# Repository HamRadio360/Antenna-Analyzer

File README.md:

# K6BEZ Antenna Analyzer

The K6BEZ antenna analyzer will provide VSWR measurements for any antenna from 1 to 30 MHz.  Frequency and VSWR is shown on the built in LCD display.  Data can optionally be sent over the USB cable to a PC running a program that will plot the VSWR on a graphical window display.
The analyzer can be programmed to scan any sub band and has built in ranges for 160m, 80m, 60m, 40m, 30m, 20m, 17m, 15m, 12m, 10m. 

For more information check out the [project website](http://www.360workbench.com/) and the [Ham Radio 360 forum](http://hamradio360.com/community/main-forum/).

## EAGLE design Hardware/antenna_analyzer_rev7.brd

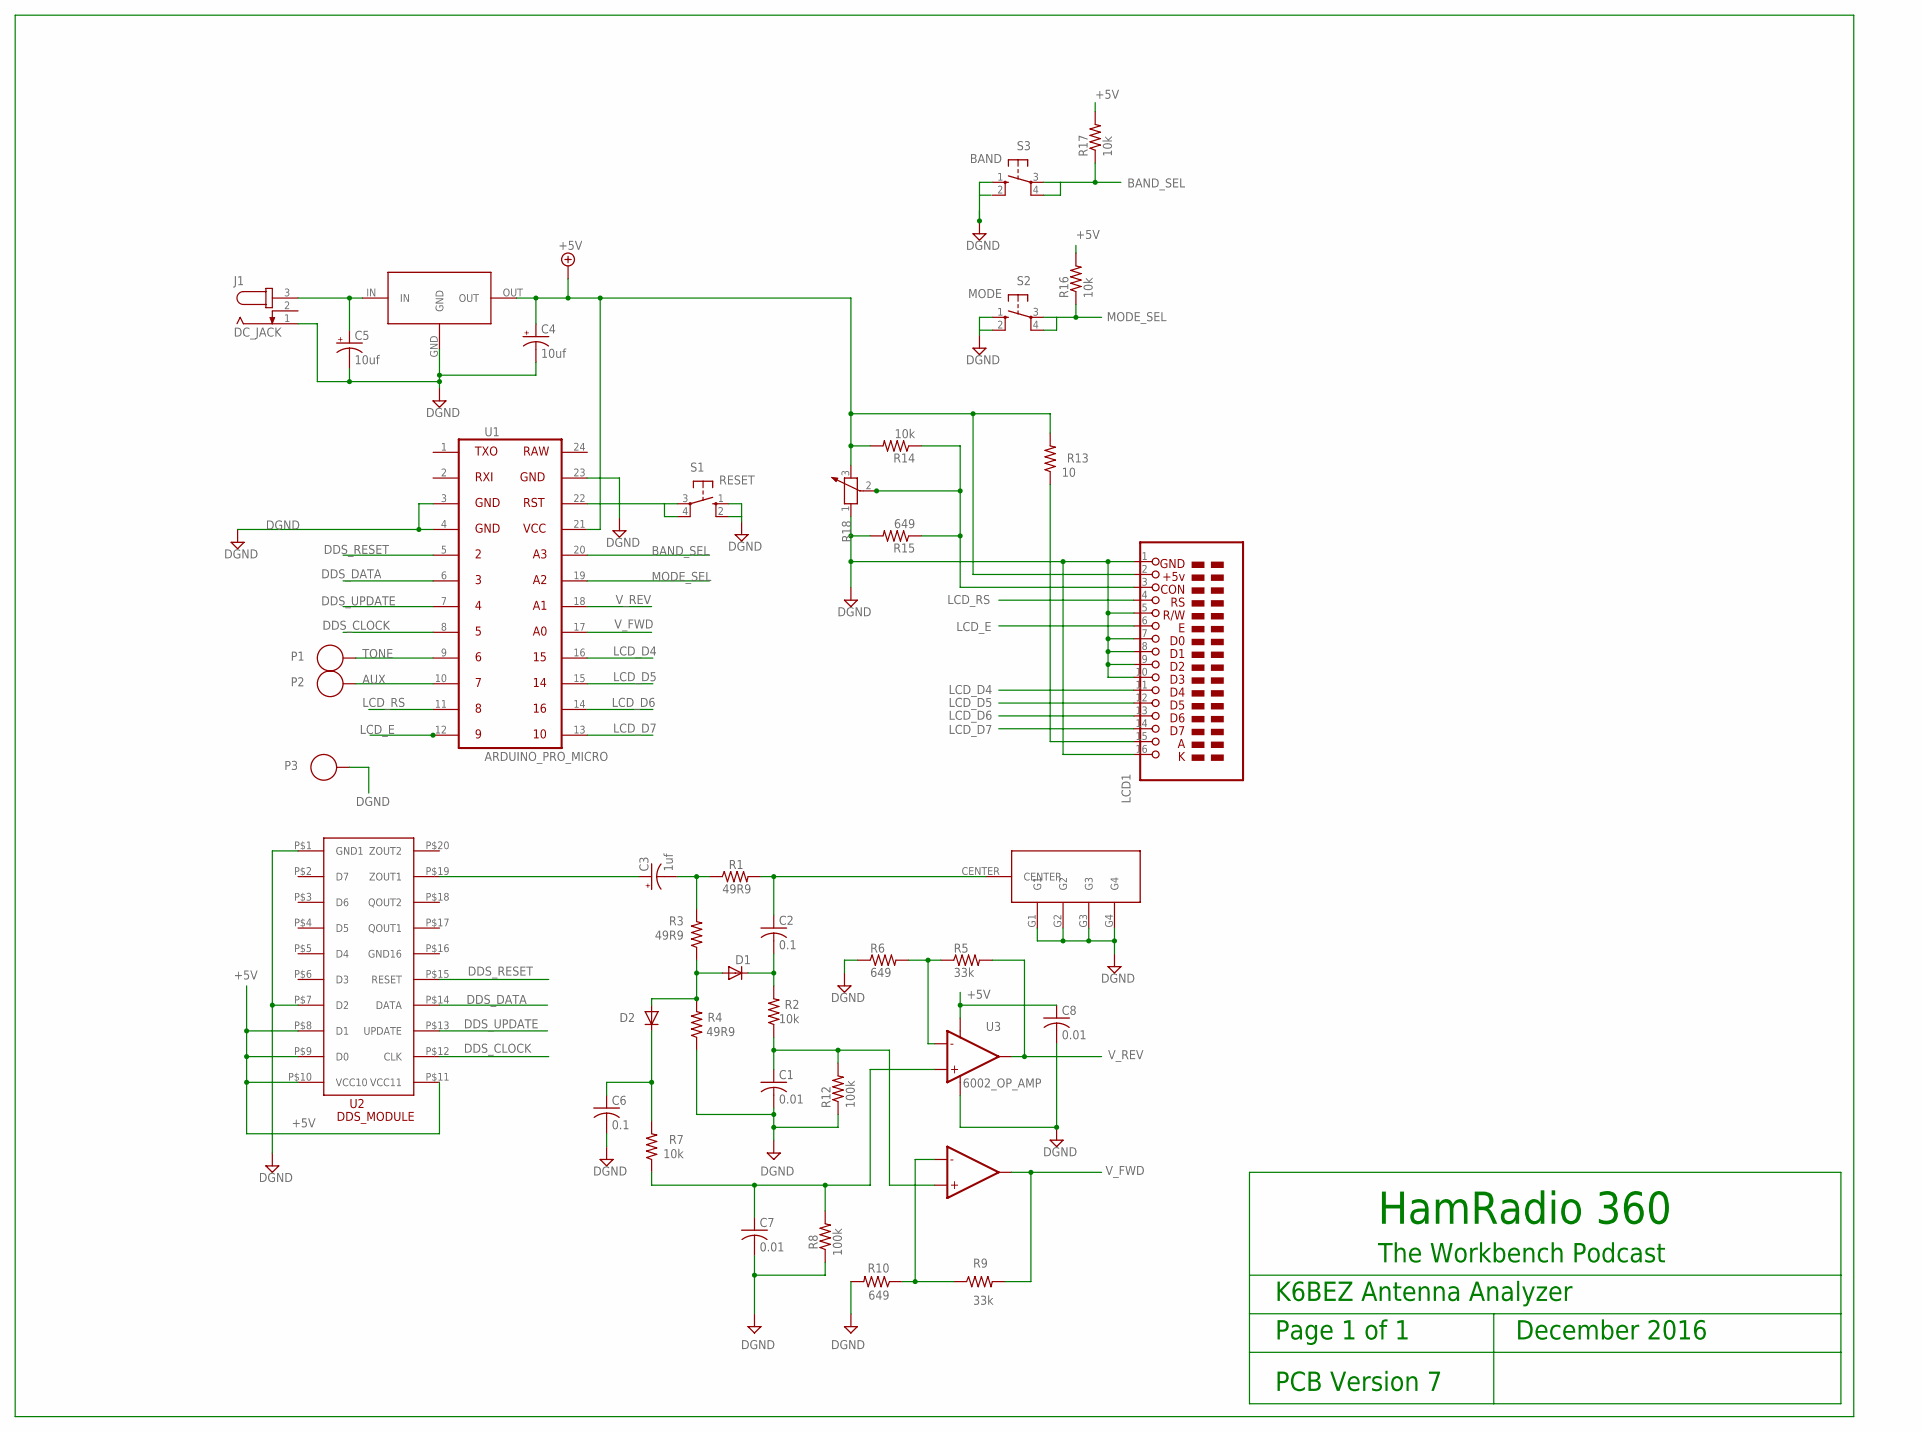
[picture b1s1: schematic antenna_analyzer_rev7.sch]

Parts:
C1, C7, C8: 0.01; C025-025X050
C2, C6: 0.1; C025-025X050
C3: 1uf; E1,8-4
C4, C5: 10uf; E1,8-4
CON1: BNC-SMALL
D1, D2: AA143; DO35-7
J1: DC_JACK; DC_COAXIAL_JACK
LCD1: LCD_2_16; LCD_2X16
P1, P2, P3: SOLDER_PAD_35_HOLE
R1, R3, R4: 49R9; 0207/10
R2, R7, R14, R16, R17: 10k; 0207/10
R5, R9: 33k; 0207/10
R6, R10, R15: 649; 0207/10
R8, R12: 100k; 0207/10
R13: 10; 0207/10
R18: R-POTENTIOMETER-3362U; 3362U
S1: RESET; B3F-10XX
S2: MODE; B3F-10XX
S3: BAND; B3F-10XX
U1: ARDUINO_PRO_MICRO
U2: AD9850_MOD; DDS_DIL
U3: 6002_OP_AMP; OP_AMP_8_PIN
U5: SWITCHING_REGULATOR

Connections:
+5V: C4.+, C8.1, LCD1.2, R13.2, R14.2, R16.2, R17.2, R18.3 (2), U1.21, U2.P$8 (D1), U2.P$9 (D0), U2.P$10 (VCC10), U2.P$11 (VCC11), U3.8 (VCC+), U5.OUT
AUX: P2.1, U1.10
BAND_SEL: R17.1, S3.3, S3.4 (P1), U1.20
DDS_CLOCK: U1.8, U2.P$12 (CLK)
DDS_DATA: U1.6, U2.P$14 (DATA)
DDS_RESET: U1.5, U2.P$15 (RESET)
DDS_UPDATE: U1.7, U2.P$13 (UPDATE)
DGND: C1.2, C4.-, C5.-, C6.2, C7.2, C8.2, CON1.G1, CON1.G2, CON1.G3, CON1.G4, J1.1, LCD1.1, LCD1.5, LCD1.7, LCD1.8, LCD1.9, LCD1.10, LCD1.16, P3.1, R4.1, R6.1, R8.1, R10.2, R12.1, R15.2, R18.1, S1.1 (S), S1.2 (S1), S2.1 (S), S2.2 (S1), S3.1 (S), U1.3, U1.4, U1.23, U2.P$1 (GND1), U2.P$7 (D2), U3.4 (VCC-), U5.GND
LCD_D4: LCD1.11, U1.16
LCD_D5: LCD1.12, U1.15
LCD_D6: LCD1.13, U1.14
LCD_D7: LCD1.14, U1.13
LCD_E: LCD1.6, U1.12
LCD_RS: LCD1.4, U1.11
MODE_SEL: R16.1, S2.3, S2.4 (P1), U1.19
unnamed: C5.+, J1.3, U5.IN
unnamed: C6.1, D2.C, R7.2
unnamed: C3.+, U2.P$19 (ZOUT1)
unnamed: C3.-, R1.1, R3.2
unnamed: D1.A, D2.A, R3.1, R4.2
unnamed: C2.1, CON1.CENTER, R1.2
unnamed: C2.2, D1.C, R2.2
unnamed: C1.1, R2.1, R12.2, U3.5 (IN+2)
unnamed: C7.1, R7.1, R8.2, U3.3 (IN+1)
unnamed: S1.3, S1.4 (P1), U1.22
unnamed: R9.1, R10.1, U3.6 (IN-2)
unnamed: R5.1, R6.2, U3.2 (IN-1)
unnamed: LCD1.15, R13.1
unnamed: LCD1.3, R14.1, R15.1, R18.2 (3)
TONE: P1.1, U1.9
V_FWD: R9.2, U1.17, U3.7 (OUT2)
V_REV: R5.2, U1.18, U3.1 (OUT1)

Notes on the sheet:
HamRadio 360
The Workbench Podcast
K6BEZ Antenna Analyzer
Page 1 of 1 December 2016
PCB Version 7

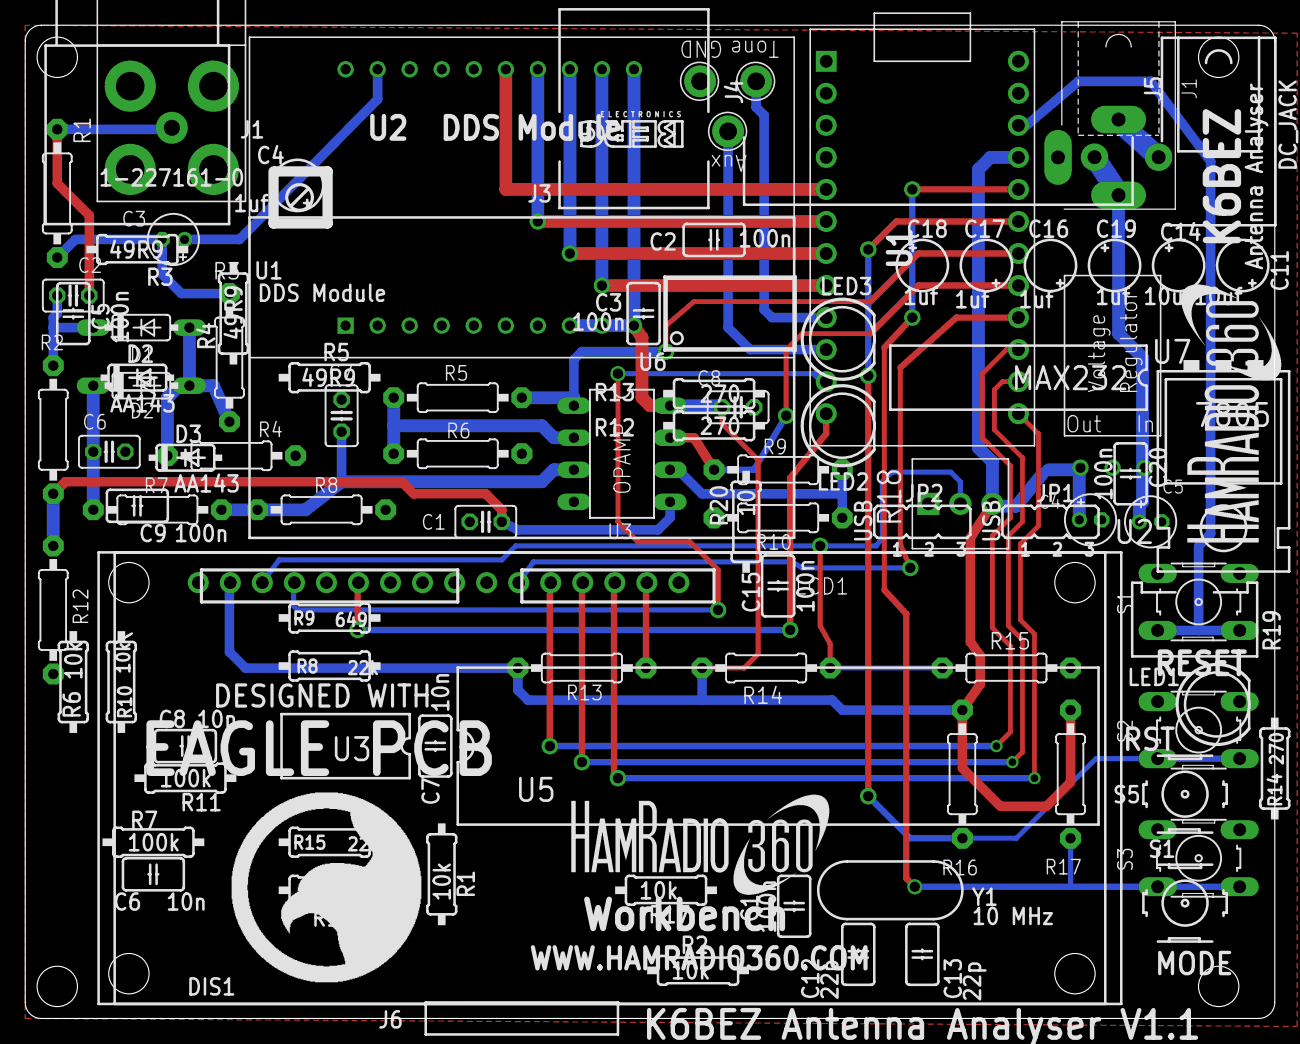
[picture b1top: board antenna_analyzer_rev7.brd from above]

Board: 2 copper layers, 99.1 x 78.7 mm, 42 parts (1 on the bottom side), 32 nets.

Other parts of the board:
U$1, U$2: CS-2016-LOGO-15MM

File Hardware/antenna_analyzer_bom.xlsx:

HamRadio 360 Workbench - K6BEZ Antenna Analyzer Bill of Materials
Type | Part | Description | Value | Digikey Part # | Est Price | Web Site
Connector | CON1 | Right angle BNC connector |  | A97569-ND | 3.88
Connector | J1 | DC power jack 2.1mm |  | CP-102AH-ND | 1.18
Capacitor | C1 | 0.1" spaced dipped mono 10% | 0.01 | 399-4260-ND | 0.24
Capacitor | C2 | 0.1" spaced dipped mono 10% | 0.1 | BC1084CT-ND | 0.22
Capacitor | C3 | Electrolytic capacitor 25v | 1uf | 493-10461-1-ND | 0.1
Capacitor | C4 | Electrolytic capacitor 25v | 10uf | P980-ND | 0.23
Capacitor | C5 | Electrolytic capacitor 25v | 10uf | P980-ND | 0.23
Capacitor | C6 | 0.1" spaced dipped mono 10% | 0.1 | BC1084CT-ND | 0.22
Capacitor | C7 | 0.1" spaced dipped mono 10% | 0.01 | 399-4260-ND | 0.24
Capacitor | C8 | 0.1" spaced dipped mono 10% | 0.01 | 399-4260-ND | 0.24
Resistor | R1 | 1/4 Watt 5% | 49.9 | 49.9XBK-ND | 0.1
Resistor | R2 | 1/4 Watt 5% | 10k | 10KQBK-ND | 0.1
Resistor | R3 | 1/4 Watt 5% | 49.9 | 49.9XBK-ND | 0.1
Resistor | R4 | 1/4 Watt 5% | 49.9 | 49.9XBK-ND | 0.1
Resistor | R5 | 1/4 Watt 5% | 649 | 649XBK-ND | 0.1
Resistor | R6 | 1/4 Watt 5% | 33k | 33KQBK-ND | 0.1
Resistor | R7 | 1/4 Watt 5% | 10k | 10KQBK-ND | 0.1
Resistor | R8 | 1/4 Watt 5% | 100k | 100KQBK-ND | 0.1
Resistor | R9 | 1/4 Watt 5% | 649 | 649XBK-ND | 0.1
Resistor | R10 | 1/4 Watt 5% | 33k | 33KQBK-ND | 0.1
Resistor | R12 | 1/4 Watt 5% | 100k | 100KQBK-ND | 0.1
Resistor | R13 | 1/4 Watt 5% | 10 | 10QBK-ND | 0.1
Resistor | R14 | 1/4 Watt 5% | 10k | 10KQBK-ND | 0.1
Resistor | R15 | 1/4 Watt 5% | 649 | 649XBK-ND | 0.1
Resistor | R16 | 1/4 Watt 5% | 10k | 10KQBK-ND | 0.1
Resistor | R17 | 1/4 Watt 5% | 10k | 10KQBK-ND | 0.1
Switch | S1 | Tactile pushbutton switch |  | 450-1650-ND | 0.1
Switch | S2 | Tactile pushbutton switch |  | 450-1650-ND | 0.1
Switch | S3 | Tactile pushbutton switch |  | 450-1650-ND | 0.1
Integrated Circuit | U3 | MCP 6002 Dual OpAmp |  | MCP6002-E/P-ND | 0.36
Integrated Circuit | U4 | 5v DC / DC converter OKI-78SR-5/1.5-W36H-C |  | 811-2692-ND | 4.31
Mechanical | X1 | 10 pin female header |  | S7043-ND | 0.85
Mechanical | X2 | 10 pin female header |  | S7043-ND | 0.85
Mechanical | X3 | 16 pin male header 0.1" pitch |  | S1011EC-16-ND | 0.4
Mechanical | X4 | 4-40 Hex standoff 1/4" long, 3/16" diameter |  | 36-1891-ND | 0.4
Mechanical | X5 | 4-40 Hex standoff 1/4" long, 3/16" diameter |  | 36-1891-ND | 0.4
Mechanical | X6 | 4-40 Hex standoff 1/4" long, 3/16" diameter |  | 36-1891-ND | 0.4
Mechanical | X7 | 4-40 Hex standoff 1/4" long, 3/16" diameter |  | 36-1891-ND | 0.4
Mechanical | X8 | 4-40 Hex standoff 1/4" long, 3/16" diameter |  | 36-1891-ND | 0.4
Mechanical | X9 | 4-40 Hex standoff 1/4" long, 3/16" diameter |  | 36-1891-ND | 0.4
Mechanical | X10 | 4-40 Hex standoff 1/4" long, 3/16" diameter |  | 36-1891-ND | 0.4
Mechanical | X11 | 4-40 Hex standoff 1/4" long, 3/16" diameter |  | 36-1891-ND | 0.4
Mechanical | X12 | 4-40 1/4" pan head philips screw |  | 36-9900-ND | 0.1
Mechanical | X13 | 4-40 1/4" pan head philips screw |  | 36-9900-ND | 0.1
Mechanical | X14 | 4-40 1/4" pan head philips screw |  | 36-9900-ND | 0.1
Mechanical | X15 | 4-40 1/4" pan head philips screw |  | 36-9900-ND | 0.1
Mechanical | X16 | 4-40 hex nut |  | 36-4694-ND | 0.08
Mechanical | X17 | 4-40 hex nut |  | 36-4694-ND | 0.08
Mechanical | X18 | 4-40 hex nut |  | 36-4694-ND | 0.08
Mechanical | X19 | 4-40 hex nut |  | 36-4694-ND | 0.08
Mechanical | X20 | 4-40 1/2" pan head philips screw |  | 36-9902-ND | 0.12
Mechanical | X21 | 4-40 1/2" pan head philips screw |  | 36-9902-ND | 0.12
Mechanical | X22 | 4-40 1/2" pan head philips screw |  | 36-9902-ND | 0.12
Mechanical | X23 | 4-40 1/2" pan head philips screw |  | 36-9902-ND | 0.12
Mechanical | X24 | 8 pin DIP socket |  | AE9986-ND | 0.18
 |  |  |  |  | 20.03
Components from Other Internet Sources
Item | Part | Description | Price | Web Site
Integrated Circuit | U1 | Arduino Pro Micro | 5.71 | http://www.dx.com/p/pro-micro-atmega-32u4-5v-16mhz-developme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
Integrated Circuit | U2 | AD9850 DDS Module | 12.1 | http://www.ebay.com/itm/AD9850-DDS-Signal-Generator-Module-0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
LCD | LCD1 | 2x16 LCD Display | 3.41 | http://www.ebay.com/itm/1602-162-16x2-Character-LCD-Display-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
Components from PackTenna
Item | Part | Description | Price | Web Site
Antenna Analyzer Parts Kit includes… |  |  | 16.8
 | PCB | Printed circuit board
 | D1 | AA143 Germanium diode
 | D2 | AA143 Germanium diode

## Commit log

2016-12-07 Added Antenna Analyzer schematic rev 7
2016-12-07 Moved schematic to Hardware
    Created a hardware folder for better organization
2016-12-09 adding in Ardunio firmware
2016-12-09 added readme placeholder
2016-12-09 added a bit to the readme
2017-01-09 added Marc Farly firmware
2017-01-09 added readme for firmware directory
2017-01-12 Added rev 7 pcb files and documentation
2017-01-12 Added original firmware and a license and readme
2017-01-12 Added a Readme for the project
2017-01-12 Updated license header
2017-01-12 Modified formatting for readability
2017-01-28 Divided standard and advanced firmwares
2017-01-28 Inital Python host program from KB5EZ
2017-01-31 Speed up acquisition time...
    Removed all delay() calls, as the AD9850 DDS has microscopic settling
    time for frequency changes and serial communications. Changes reduce
    acquisition time for a 1-30 MHz scan from 11.74 seconds to 1.65 seconds.
2017-02-02 Compensation/calibration routines
    - added automated calibration routines to setup(). Measures the FWD/REV
    ADC values when no input is appled to compensate for idle noise. These
    offsets are subtracted from the later FWD/REV reads.
    - added diode mismatch compensation values, empirically read at the ADC
    when a shorted antenna port is being drive. The ratio of measured value
    (REV/FWD) is used to compensate the FWD value.
2017-02-03 Refined compensation routines, prettified the display, and code cleanup
    - The two compensation ratios (Gain and Diode) turned out to be
    frequency dependent, requiring equations to determine the compenstation
    ratio during the sweep (left in the mean value and linear methods of
    compensation as comments).
    - Changed display routines to provide a more readable output with fixed
    sizes and scaling/
